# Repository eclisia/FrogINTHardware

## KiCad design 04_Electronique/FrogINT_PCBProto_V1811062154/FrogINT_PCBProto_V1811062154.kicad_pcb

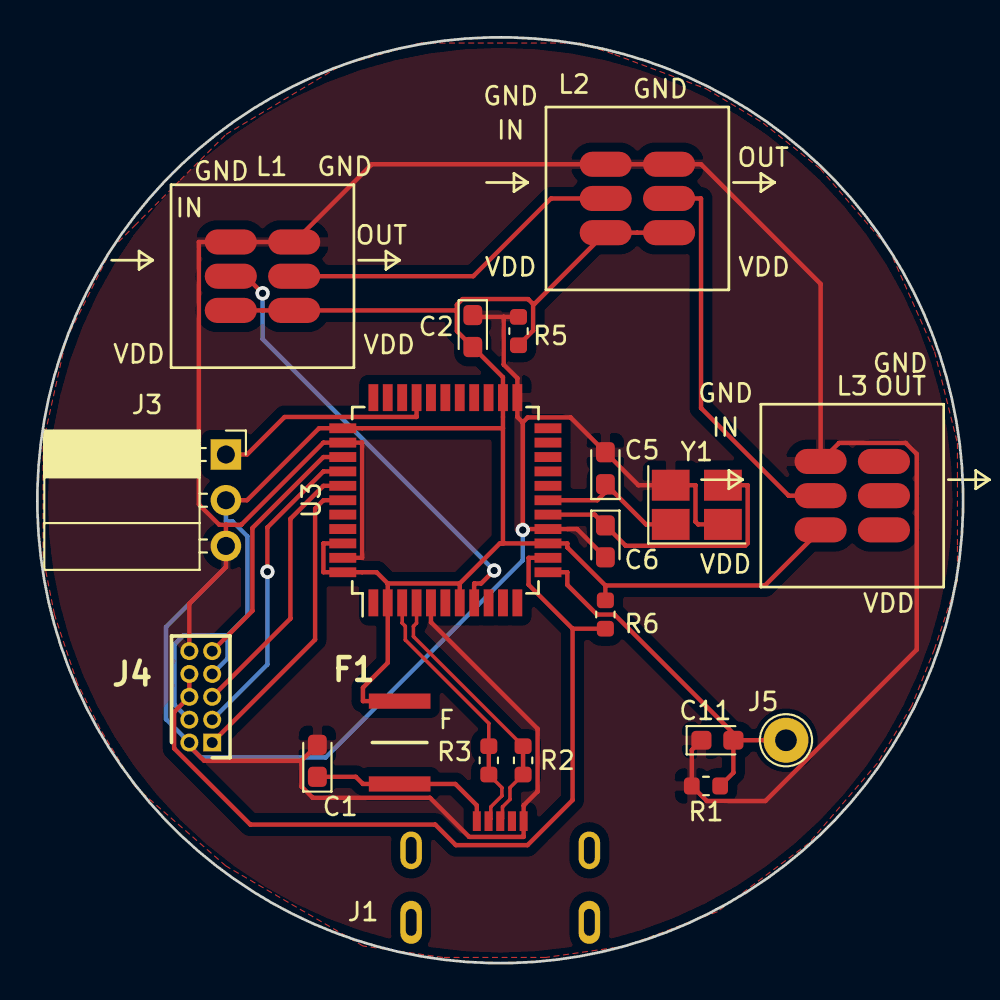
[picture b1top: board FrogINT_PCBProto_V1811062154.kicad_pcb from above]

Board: 2 copper layers, 51.4 x 51.4 mm, 20 parts (0 on the bottom side), 17 nets.

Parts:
C1: 22µF; CP_EIA-2012-12_Kemet-R
C2: 100nF; CP_EIA-2012-12_Kemet-R
C5, C6, C11: 22pF; CP_EIA-2012-12_Kemet-R
F1: Polyfuse MF-MSMF050-2; FUSC4632X85N
J1: USB_B_Mini; 47642-0001_Molex_USB
J3: Conn_01x03; PinSocket_1x03_P2.54mm_Horizontal
J4: JTAG; JTAG_HDRV10W41P127_2X5_676X325X510P
J5: Conn_01x01_Female; TestPoint_THTPad_D2.5mm_Drill1.2mm
L1, L2, L3: LED; WS2812-LED_HeatSink
R1, R5, R6: 10k; R_0603_1608Metric
R2, R3: 22; R_0603_1608Metric
U3: ATmega16U4-AU; TQFP-44_10x10mm_P0.8mm
Y1: XTal TSX-3225 16MHz; Crystal_SMD_SeikoEpson_TSX3225-4Pin_3.2x2.5mm_HandSoldering

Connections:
+3V3: C2.2, F1.1, J3.2, J4.4, J4.7, L1.3, L1.6, L2.3, L2.6, L3.3, R5.1, R6.1, U3.2, U3.7, U3.14, U3.24, U3.34, U3.42, U3.44
/D+: J1.3, R2.1, R2.2, U3.4
/D-: J1.2, R3.1, R3.2, U3.3
/Input_Int_Touch: J3.1, U3.30
/Input_Interrupt: C11.2, J5.1, R1.1, U3.12
/reset: J4.6, J4.8, R6.2, U3.13
GND: C1.2, C2.1, C5.2, C6.2, C11.1, J1.5, J3.3, J4.2, J4.10, L1.1, L1.4, L2.1, L2.4, L3.1, R1.2, R5.2, U3.5, U3.15, U3.23, U3.35, U3.43, Y1.2, Y1.4
unnamed: C1.1, F1.2, J1.1
unnamed: C5.1, U3.17, Y1.1
unnamed: C6.1, U3.16, Y1.3
unnamed: J4.1, U3.39
unnamed: J4.3, U3.37
unnamed: J4.5, U3.38
unnamed: J4.9, U3.36
unnamed: L1.2, U3.8
unnamed: L1.5, L2.2
unnamed: L2.5, L3.2

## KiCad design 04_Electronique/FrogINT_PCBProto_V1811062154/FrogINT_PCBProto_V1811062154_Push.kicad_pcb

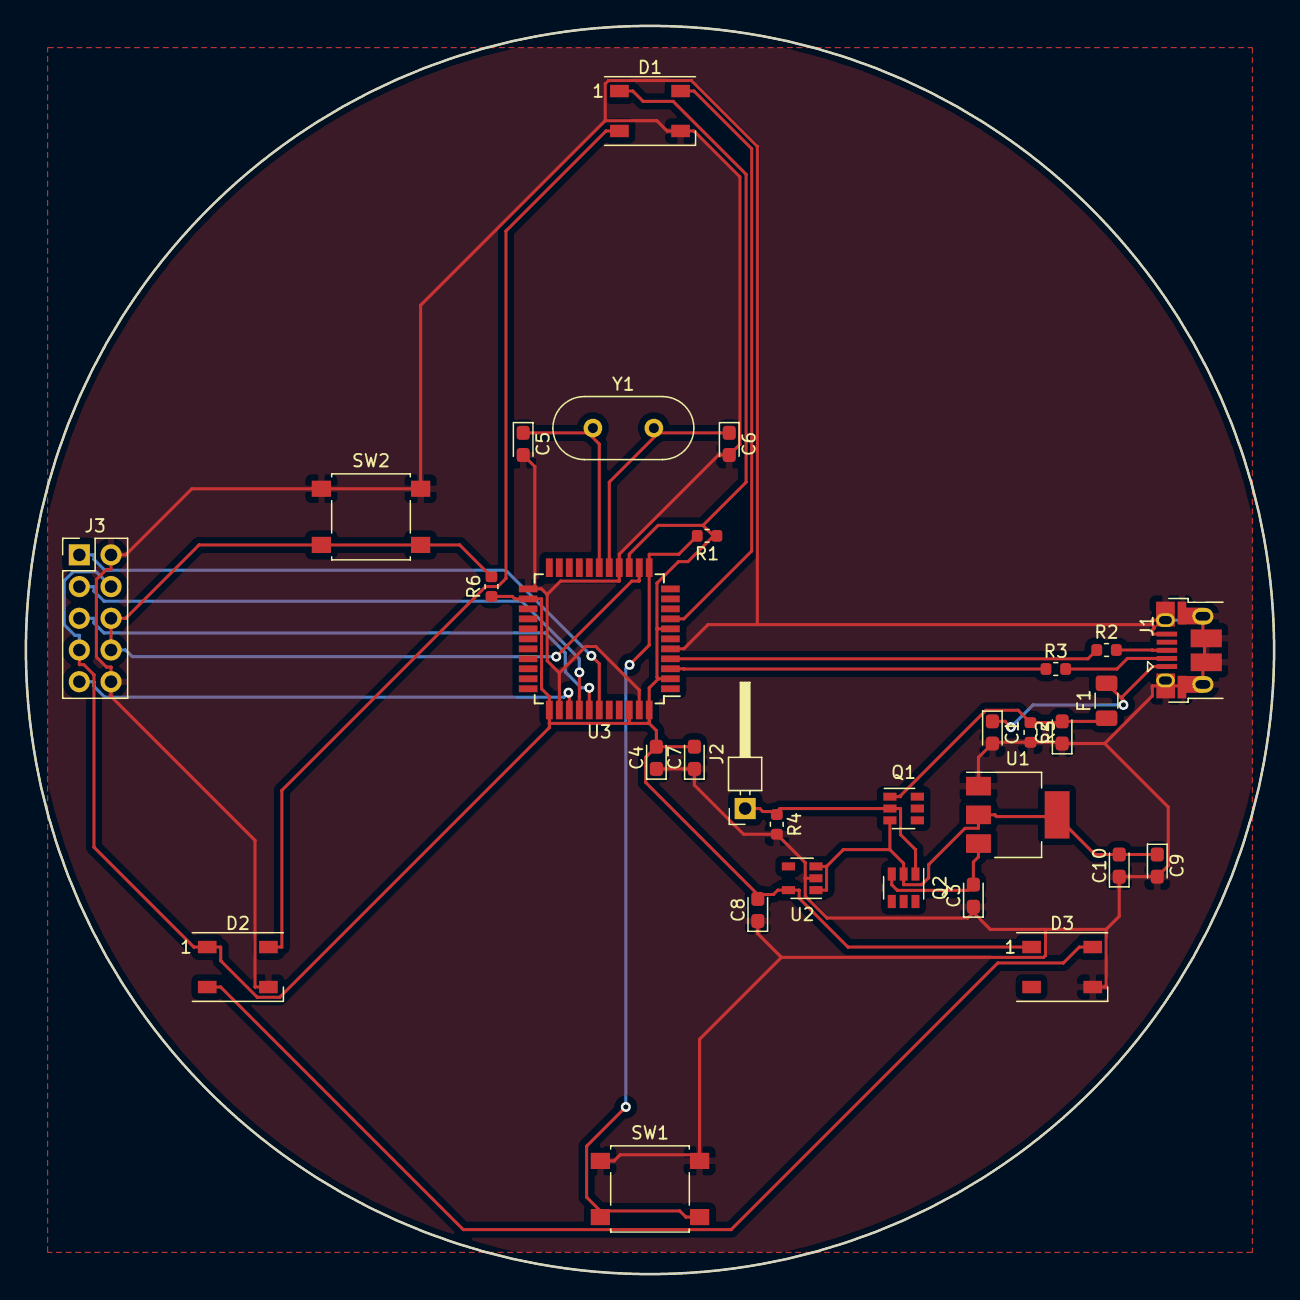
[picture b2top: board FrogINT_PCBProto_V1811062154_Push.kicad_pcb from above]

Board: 2 copper layers, 100.0 x 100.0 mm, 31 parts (0 on the bottom side), 22 nets.

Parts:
C1, C9: 22µF; CP_EIA-2012-12_Kemet-R
C2, C3, C10: 100nF; CP_EIA-2012-12_Kemet-R
C4, C7: 0.1µF; CP_EIA-2012-12_Kemet-R
C5, C6: 22pF; CP_EIA-2012-12_Kemet-R
C8: 1µF; CP_EIA-2012-12_Kemet-R
D1, D2, D3: WS2812B; LED_WS2812B_PLCC4_5.0x5.0mm_P3.2mm
F1: Polyfuse MF-MSMF050-2; Fuse_1206_3216Metric
J1: USB_B_Mini; USB_Micro-B_Amphenol_10103594-0001LF_Horizontal
J2: Conn_01x01_Female; PinHeader_1x01_P2.54mm_Horizontal
J3: AVR-JTAG-10; PinHeader_2x05_P2.54mm_Vertical
Q1, Q2: PMV48XP; SOT-23-6
R1, R4, R5, R6: 10k; R_0603_1608Metric
R2, R3: 22; R_0603_1608Metric
SW1, SW2: SW_SPST; SW_SPST_B3S-1000
U1: NCP1117-5.0_SOT223; SOT-223-3_TabPin2
U2: LP2985-3.3; SOT-23-5
U3: ATmega16U4RC-AU; TQFP-44_10x10mm_P0.8mm
Y1: 16MHz; Crystal_HC49-U_Vertical

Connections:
+3V3: C4.2, C7.2, C8.2, D1.1, D2.1, D3.1, J3.4, J3.7, R1.1, R6.1, U2.5, U3.2, U3.7, U3.14, U3.24, U3.34, U3.42, U3.44
+5V: C9.1, C10.2, Q1.3, Q2.2, U1.2, U2.1, U2.3
/D+: R2.1, U3.4
/D-: R3.1, U3.3
/Input_Interrupt: R1.2, SW1.2, U3.12
/Vin: J2.1, Q1.2, Q2.1, R4.1
/reset: J3.6, J3.8, R6.2, SW2.2, U3.13
GND: C1.2, C2.1, C3.1, C4.1, C5.2, C6.2, C7.1, C8.1, C9.2, C10.1, D1.3, D2.3, D3.3, J1.5, J1.6, J3.2, J3.10, R4.2, R5.2, SW1.1, SW2.1, U1.1, U2.2, U3.5, U3.15, U3.23, U3.35, U3.43
unnamed: C1.1, F1.2, J1.1
unnamed: C3.2, Q2.3, U1.3
unnamed: C5.1, U3.17, Y1.1
unnamed: C6.1, U3.16, Y1.2
unnamed: D1.2, D2.4
unnamed: D1.4, U3.8
unnamed: D2.2, D3.4
unnamed: J1.2, R3.2
unnamed: J1.3, R2.2
unnamed: J3.1, U3.39
unnamed: J3.3, U3.37
unnamed: J3.5, U3.38
unnamed: J3.9, U3.36
VBUS: C2.2, F1.1, Q1.1, R5.1

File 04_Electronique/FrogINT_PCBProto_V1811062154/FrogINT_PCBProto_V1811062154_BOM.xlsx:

Component,Description,Part,References,Value,Footprint,Quantity Per PCB,Datashee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
1,Unpolarized capacitor,C,C4 C7,0.1ÂµF,CP_EIA-2012-12_Kemet-R,2,,,,,,,,
2,Unpolarized capacitor,C,C2 C3 C10 C12,100nF,CP_EIA-2012-12_Kemet-R,4,,,,,,,,
3,Unpolarized capacitor,C,C8,1ÂµF,CP_EIA-2012-12_Kemet-R,1,,,,,,,,
4,Unpolarized capacitor,C,C5 C6 C11,22pF,CP_EIA-2012-12_Kemet-R,3,,,,,,,,
5,Polarized capacitor,CP,C1 C9,22ÂµF,CP_EIA-2012-12_Kemet-R,2,,,,,,,,
6,RGB LED with integrated controller,WS2812B,D1 D2 D3,WS2812B,LED_WS2812B_PLCC4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
7,"Resettable fuse, polymeric positive temperature coefficient, small symbol",P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
8,,TTP223-BA6-SamacSys_Parts,IC1,TTP223-BA6,SOT95P285X126-6N,1,https://radiokot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
9,Atmel 10-pin JTAG connector,AVR-JTAG-10,J3,AVR-JTAG-10,PinHeader_2x05_P2.54mm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
10,"Generic connector, single row, 01x01, script generated (kicad-library-utils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
11,,USB_B_Mini-Connector_FTA,J1,USB_B_Mini,USB_Micro-B_Amphenol_10103594-0001LF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
12,"P-MOSFET transistor, drain/gate/source",Q_PMOS_DGS,Q1 Q2,PMV48XP,SOT-23-6,2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
13,Resistor,R,R1 R4 R5 R6,10k,R_0603_1608Metric,4,,,,,,,,
14,Resistor,R,R2 R3,22,R_0603_1608Metric,2,,,,,,,,
15,,SKQGAKE010-SamacSys_Parts,S1 S2,SKQGAKE010,SKQGAKE010,2,http://uk.rs-online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
16,,TouchSense-FTA_FrogINT_library,TS1,TouchSense,CapacitiveTouchSense_Bottom_1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
17,,ATmega16U4RC-AU,U3,ATmega16U4RC-AU,TQFP-44_10x10mm_P0.8mm,1,,,,,,,,
18,"150mA 16V Low-noise Low-dropout Regulator With Shutdown, 1.8V output voltag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
19,"1A Low Dropout regulator, positive, 1.5V fixed output, SOT-223",NCP1117-5.0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
20,Two pin crystal,Crystal,Y1,16MHz,Crystal_HC49-U_Vertical,1,,,,,,,,
Component Groups:,20
Component Count:,35
Fitted Components:,35
Number of PCBs:,1
Total components:,35
Schematic Version:,Rev-00
Schematic Date:,2018-11-15
BoM Date:,21/01/2019 14:16:21
Schematic Source:,D:\Users\taintuf\Documents\04_Travail\04-17_FabLab\01_Concour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
KiCad Version:,Eeschema (5.0.1)-3

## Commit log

2018-11-06 FirstCommit with Kicad project and files creation
2018-11-06 Ajout de documentation de référence - design Lilypad Arduino
2018-11-06 Modification librairie AVR ATmega16U4-AU pour obtenir un symbol personnalisé avec réorganisation des pins pour meilleures clareté dans le schéma.
    Création d'une carte MindMap pour ordonner les idées.
2018-11-12 Creation d'une version Draft du schéma
2018-11-17 Création version 01 du schéma pour impression Chine
2018-11-27 First Prototype realization concerning the PCB, BOM and other manufacturing files.
    This prototype could be use with Chinese partner for "Request For Quotation" process.
2018-11-27 Finalisation du routage + création d'un nouveau routage "Push" pour tester une nouvelle implémentation + Ajout d'un Logo en silkscreen & Copper.
2018-11-28 Ajout d'un Logo-FrogINT en tant qu'Image et que module pour l'inclure sur le PCB et SilkScreen
    Ajout d'une version "Push" du PCB avec l'utilisation de Freerouting - autoroutage.
2018-12-17 Add of the git ignore file in order to remove "Documentation" folder from tracking
2018-12-17 Update of the gitignore file
2018-12-17 Update of gitignore file with #comments
2018-12-17 Update of the gitignore
2019-01-07 Creation d'un touch Pad et Ajout du composant TTP223.
    Création des librairies équivalentes pour le pad dans Samsac.
2019-01-14 ***Commit du 14/01/2019 suite aux modifications du 11/01/2019
    • Création d'un nouveau composant (schéma + PCB) TouchSense sur la librairie FTA (et non plus Samacsys)
    • Ajout de ce composant dans le design courant
2019-01-14 ***Commit du 14/01/2019 :
    - Mise à jour des micro switch - choix d'une référence plus petites.
    - Mise à jour des librairies
    - Ajout des librairies SamacSys directement dans le projet
2019-01-22 Commit 22/01/2019 : Version 03 de la BOM + Intégration 100% du PCB pour réalisation chiffrage
    Mise à jour des librairies et des chemins relatifs des librairies de composants
    Remplacement du Point de Contrôle type pin header FE 2.54mm par un PAD sur le PCB
    Ajout des sérigraphies définitives.
2019-01-28 HotFix : Erreur du précédent commit car tous les fichiers ont été cryptés.
2019-02-05 Commit du 05/02/2019 :
    Création d'une nouvelle forme de PCB,
    Placement sommaire des composants,
    Utilisation de Freerouting.jar pour effectuer une partie du routage.
2019-02-12 12/02/2019 : Remplacement des gros boutons par des plus petits
    Impact :
    Mise à jour du fichier Excel FrogINT_BOM_V03-Commit-22-01-2019_RFQ_RS.xlsx suite à la mise à jour de la BOM (Attention pour les chiffrage en cours)
    Création des fichiers sources mécaniques pour ce nouveau Switch_PTS810SJG250SMTRLFS
    Mise à jour des références des librairies (pointeur).
    Déplacement partiel de la librairie SamacSys_Parts directement dans la "racine" du projet (et non plus dans l'arborescence C: etc.)
2019-02-26 26/02/2019 : Déplacement de la librairie SamacSys dans le répertoire du projet.
2019-03-12 Modification mineur pour réaliser des exports graphiques uniquement.
2019-03-14 Creation d'une archive avec la version initiale de la BOM. La future version apportera des changements majeurs.
2019-03-14 Commit du 14/03/2019 :
    - Remplacement header JTAG 2.54 par un header au format 1.27 afin de réduire taille sur le PCB
    - Suppression des composants ainsi que du TouchPAD sur le PCB, au profit d'un simple connecteur header 2.54 ==> Permettra le raccordement directement des modules chinois
    - Modification de la librairie du connecteur USB 47642.
    - Modification du footprint du connecteur USB 47642 afin de tenir compte de l'aspect "Throughole".
2019-03-26 Commit du 26/03/2019 en vue de la Release V2.
    Décision de figer une release V2 avant de modifier complètement le circuit et le PCB.
2019-03-26 Commit du 26/03/2019 :
    - Refonte du PCB --> passage en circulaire de 3,8mm de diamètre
    - Mise à jour des librairies avec notamment création de la librairie atmega16u4-au
    - Mise à jour de la librairie sur le connecteur USB pour ajouter les CTRL.YBCK -> limite du composant
    - Suppression de la fonction d'alimention 3V3 au profit d'une seule alimentation en 5V. Attention, il faut cependant corriger le naming
    - Changement du connecteur pour le TouchSensor (femelle)
    - ajout d'un R/C + pad pour souder directement une antenne pour tester le Sensor Capacitif
2019-04-02 Evolution de la V3 :
    + Creation d'un modèle pour les LED WS2812 avec HeatSink (Footprint + meca3D)
    + Creation d'un modèle pour Fusible (Footprint + Meca3D)
    Autre évolution majeure :
    • Ligne USB – Faire une paire différentielle
    • Supprimer le switch « normal » pour ne conserver que le switch « reset ».
    o OK
